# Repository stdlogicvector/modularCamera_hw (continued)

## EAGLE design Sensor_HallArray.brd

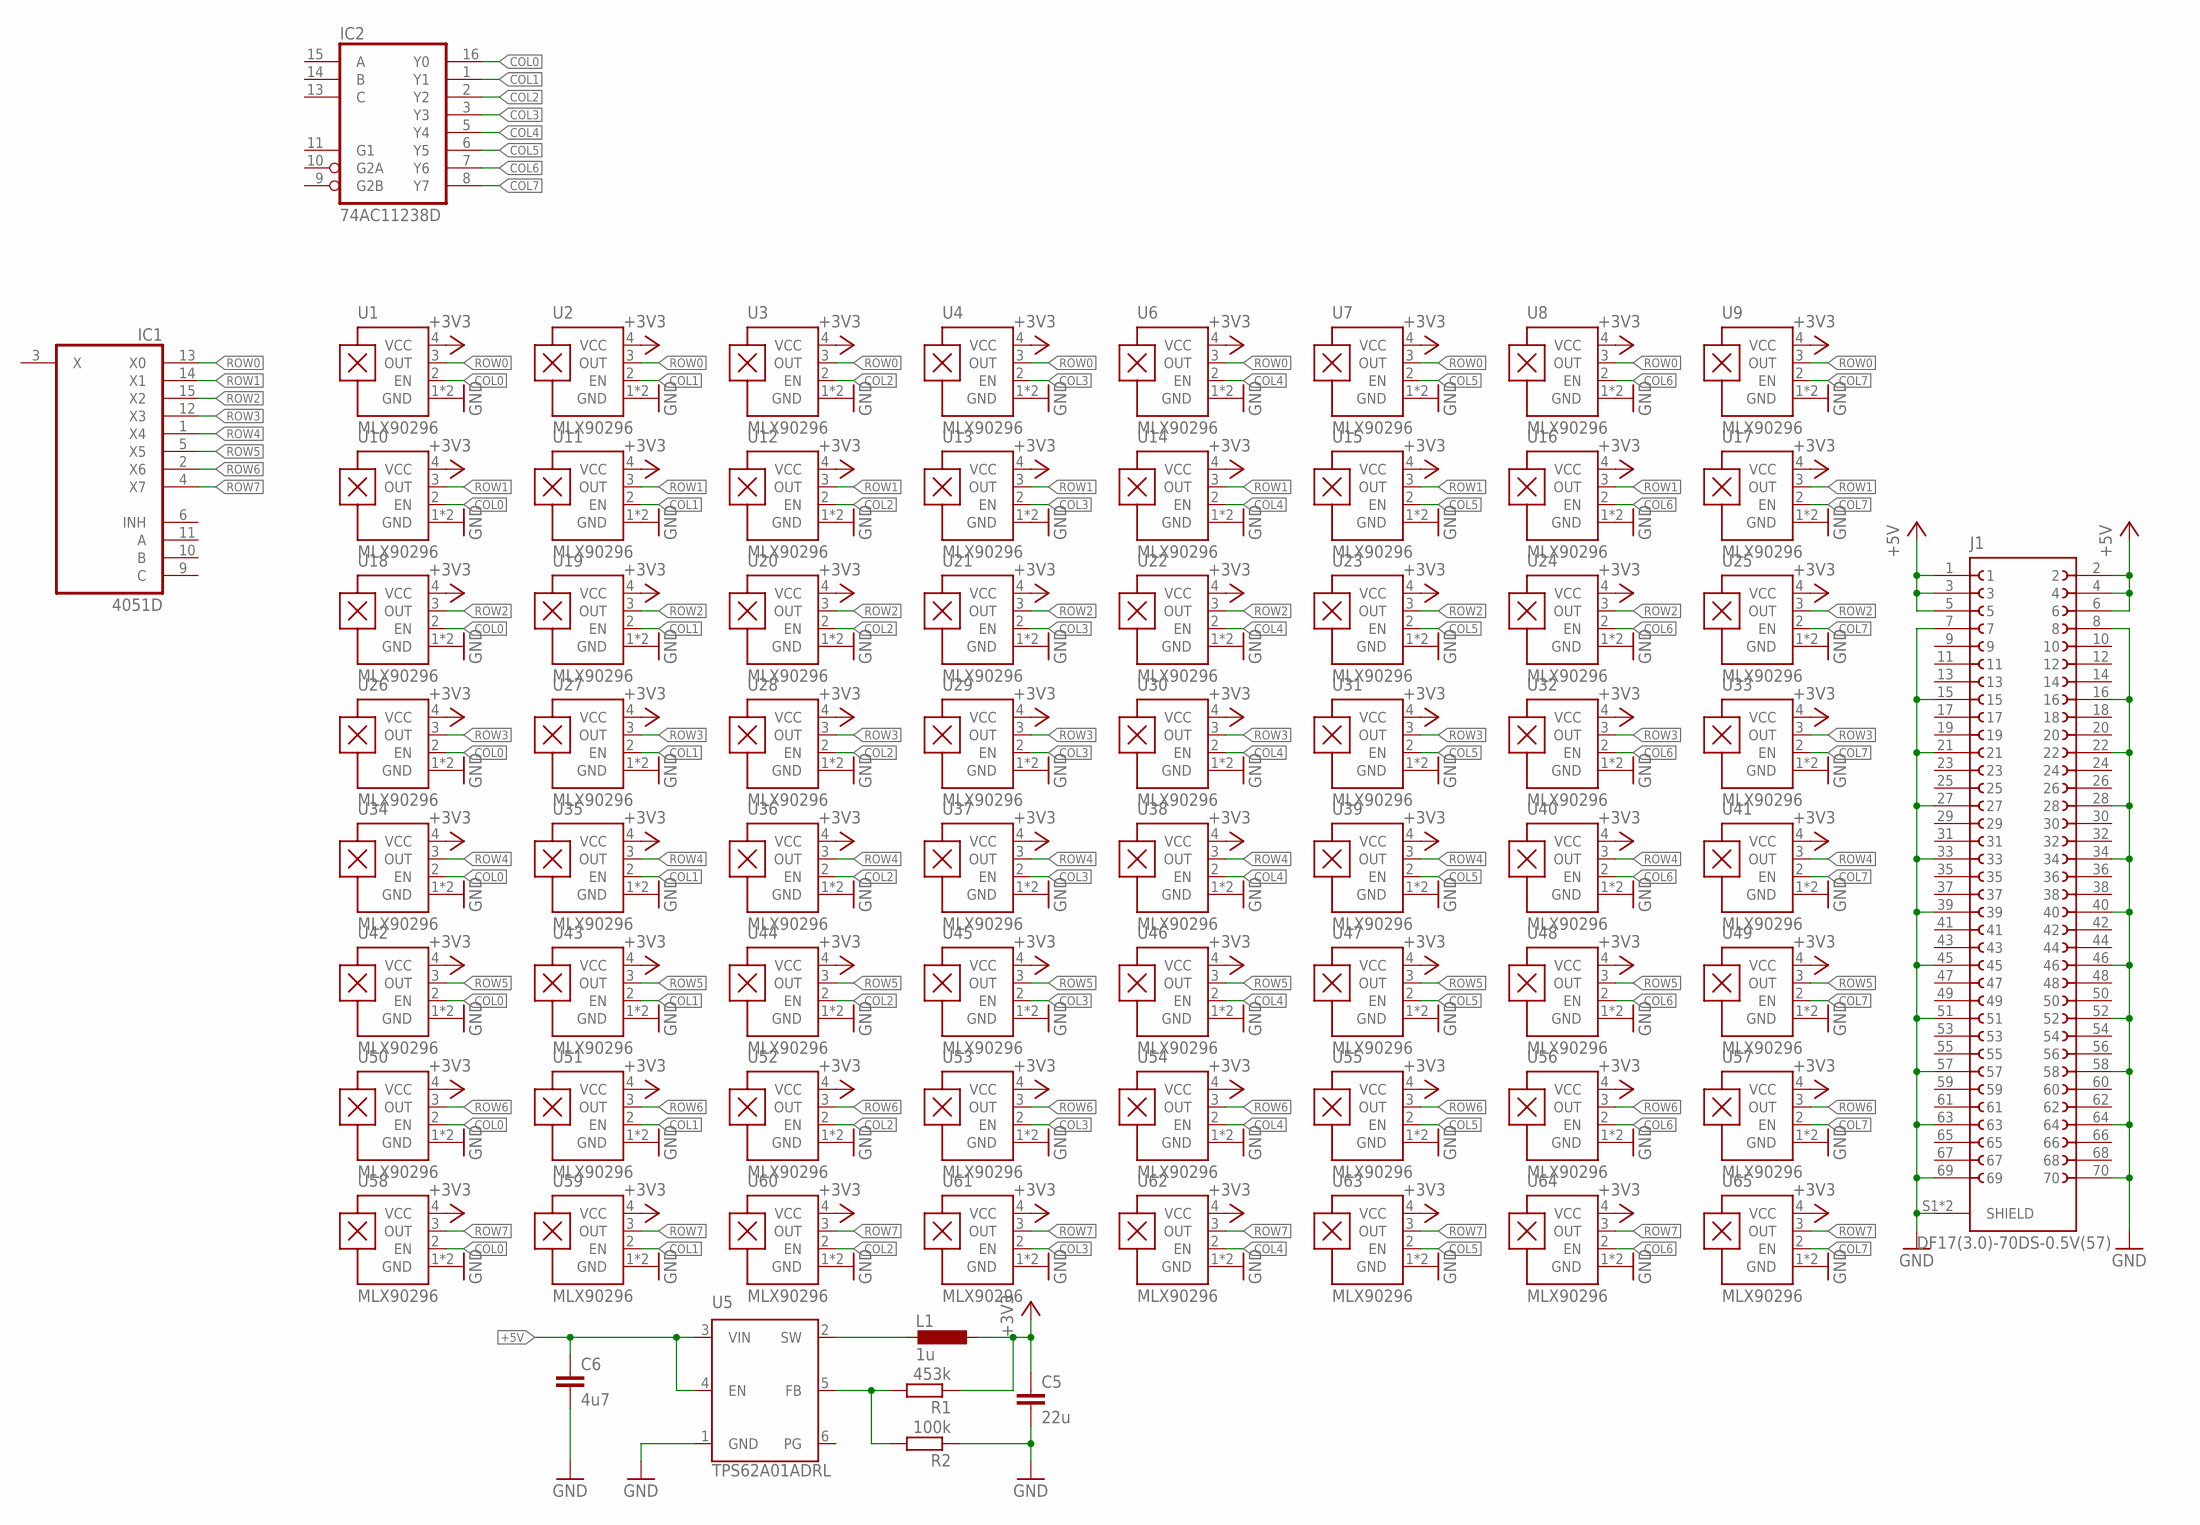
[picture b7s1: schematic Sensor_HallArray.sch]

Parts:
C5: 22u; C0603; LCSC C109448
C6: 4u7; C0603; LCSC C19666
IC1: 4051D; SO16
IC2: 74AC11238D; SO16
J1: DF17(3.0)-70DS-0.5V(57)
L1: 1u; L1008; MPN LQM2HPN1R0MG0L; DIGIKEY 490-5112-1-ND
R1: 453k; R0402; LCSC C137978
R2: 100k; R0402; DIGIKEY RMCF0402FT100KCT-ND
U1, U2, U3, U4, U6, U7, U8, U9, U10, U11, U12, U13, U14, U15, U16, U17, U18, U19, U20, U21, U22, U23, U24, U25, U26, U27, U28, U29, U30, U31, U32, U33, U34, U35, U36, U37, U38, U39, U40, U41, U42, U43, U44, U45, U46, U47, U48, U49, U50, U51, U52, U53, U54, U55, U56, U57, U58, U59, U60, U61, U62, U63, U64, U65: MLX90296; DFN120X160X40-4
U5: TPS62A01ADRL; SOTFL50P160X60-6N; DIGIKEY 296-TPS62A01ADRLRCT-ND

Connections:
+3V3: C5.1, L1.1, R1.1, U1.4 (VCC), U2.4 (VCC), U3.4 (VCC), U4.4 (VCC), U6.4 (VCC), U7.4 (VCC), U8.4 (VCC), U9.4 (VCC), U10.4 (VCC), U11.4 (VCC), U12.4 (VCC), U13.4 (VCC), U14.4 (VCC), U15.4 (VCC), U16.4 (VCC), U17.4 (VCC), U18.4 (VCC), U19.4 (VCC), U20.4 (VCC), U21.4 (VCC), U22.4 (VCC), U23.4 (VCC), U24.4 (VCC), U25.4 (VCC), U26.4 (VCC), U27.4 (VCC), U28.4 (VCC), U29.4 (VCC), U30.4 (VCC), U31.4 (VCC), U32.4 (VCC), U33.4 (VCC), U34.4 (VCC), U35.4 (VCC), U36.4 (VCC), U37.4 (VCC), U38.4 (VCC), U39.4 (VCC), U40.4 (VCC), U41.4 (VCC), U42.4 (VCC), U43.4 (VCC), U44.4 (VCC), U45.4 (VCC), U46.4 (VCC), U47.4 (VCC), U48.4 (VCC), U49.4 (VCC), U50.4 (VCC), U51.4 (VCC), U52.4 (VCC), U53.4 (VCC), U54.4 (VCC), U55.4 (VCC), U56.4 (VCC), U57.4 (VCC), U58.4 (VCC), U59.4 (VCC), U60.4 (VCC), U61.4 (VCC), U62.4 (VCC), U63.4 (VCC), U64.4 (VCC), U65.4 (VCC)
+5V: C6.1, J1.1, J1.2, J1.3, J1.4, J1.5, J1.6, U5.3 (VIN), U5.4 (EN)
COL0: IC2.16 (Y0), U1.2 (EN), U10.2 (EN), U18.2 (EN), U26.2 (EN), U34.2 (EN), U42.2 (EN), U50.2 (EN), U58.2 (EN)
COL1: IC2.1 (Y1), U2.2 (EN), U11.2 (EN), U19.2 (EN), U27.2 (EN), U35.2 (EN), U43.2 (EN), U51.2 (EN), U59.2 (EN)
COL2: IC2.2 (Y2), U3.2 (EN), U12.2 (EN), U20.2 (EN), U28.2 (EN), U36.2 (EN), U44.2 (EN), U52.2 (EN), U60.2 (EN)
COL3: IC2.3 (Y3), U4.2 (EN), U13.2 (EN), U21.2 (EN), U29.2 (EN), U37.2 (EN), U45.2 (EN), U53.2 (EN), U61.2 (EN)
COL4: IC2.5 (Y4), U6.2 (EN), U14.2 (EN), U22.2 (EN), U30.2 (EN), U38.2 (EN), U46.2 (EN), U54.2 (EN), U62.2 (EN)
COL5: IC2.6 (Y5), U7.2 (EN), U15.2 (EN), U23.2 (EN), U31.2 (EN), U39.2 (EN), U47.2 (EN), U55.2 (EN), U63.2 (EN)
COL6: IC2.7 (Y6), U8.2 (EN), U16.2 (EN), U24.2 (EN), U32.2 (EN), U40.2 (EN), U48.2 (EN), U56.2 (EN), U64.2 (EN)
COL7: IC2.8 (Y7), U9.2 (EN), U17.2 (EN), U25.2 (EN), U33.2 (EN), U41.2 (EN), U49.2 (EN), U57.2 (EN), U65.2 (EN)
GND: C5.2, C6.2, IC1.8 (GND), IC2.4 (GND), J1.7, J1.8, J1.15, J1.16, J1.21, J1.22, J1.27, J1.28, J1.33, J1.34, J1.39, J1.40, J1.45, J1.46, J1.51, J1.52, J1.57, J1.58, J1.63, J1.64, J1.69, J1.70, J1.S1 (SHIELD), J1.S2 (SHIELD), R2.1, U1.1 (GND), U1.E (GND), U2.1 (GND), U2.E (GND), U3.1 (GND), U3.E (GND), U4.1 (GND), U4.E (GND), U5.1 (GND), U6.1 (GND), U6.E (GND), U7.1 (GND), U7.E (GND), U8.1 (GND), U8.E (GND), U9.1 (GND), U9.E (GND), U10.1 (GND), U10.E (GND), U11.1 (GND), U11.E (GND), U12.1 (GND), U12.E (GND), U13.1 (GND), U13.E (GND), U14.1 (GND), U14.E (GND), U15.1 (GND), U15.E (GND), U16.1 (GND), U16.E (GND), U17.1 (GND), U17.E (GND), U18.1 (GND), U18.E (GND), U19.1 (GND), U19.E (GND), U20.1 (GND), U20.E (GND), U21.1 (GND), U21.E (GND), U22.1 (GND), U22.E (GND), U23.1 (GND), U23.E (GND), U24.1 (GND), U24.E (GND), U25.1 (GND), U25.E (GND), U26.1 (GND), U26.E (GND), U27.1 (GND), U27.E (GND), U28.1 (GND), U28.E (GND), U29.1 (GND), U29.E (GND), U30.1 (GND), U30.E (GND), U31.1 (GND), U31.E (GND), U32.1 (GND), U32.E (GND), U33.1 (GND), U33.E (GND), U34.1 (GND), U34.E (GND), U35.1 (GND), U35.E (GND), U36.1 (GND), U36.E (GND), U37.1 (GND), U37.E (GND), U38.1 (GND), U38.E (GND), U39.1 (GND), U39.E (GND), U40.1 (GND), U40.E (GND), U41.1 (GND), U41.E (GND), U42.1 (GND), U42.E (GND), U43.1 (GND), U43.E (GND), U44.1 (GND), U44.E (GND), U45.1 (GND), U45.E (GND), U46.1 (GND), U46.E (GND), U47.1 (GND), U47.E (GND), U48.1 (GND), U48.E (GND), U49.1 (GND), U49.E (GND), U50.1 (GND), U50.E (GND), U51.1 (GND), U51.E (GND), U52.1 (GND), U52.E (GND), U53.1 (GND), U53.E (GND), U54.1 (GND), U54.E (GND), U55.1 (GND), U55.E (GND), U56.1 (GND), U56.E (GND), U57.1 (GND), U57.E (GND), U58.1 (GND), U58.E (GND), U59.1 (GND), U59.E (GND), U60.1 (GND), U60.E (GND), U61.1 (GND), U61.E (GND), U62.1 (GND), U62.E (GND), U63.1 (GND), U63.E (GND), U64.1 (GND), U64.E (GND), U65.1 (GND), U65.E (GND)
unnamed: R1.2, R2.2, U5.5 (FB)
unnamed: L1.2, U5.2 (SW)
ROW0: IC1.13 (X0), U1.3 (OUT), U2.3 (OUT), U3.3 (OUT), U4.3 (OUT), U6.3 (OUT), U7.3 (OUT), U8.3 (OUT), U9.3 (OUT)
ROW1: IC1.14 (X1), U10.3 (OUT), U11.3 (OUT), U12.3 (OUT), U13.3 (OUT), U14.3 (OUT), U15.3 (OUT), U16.3 (OUT), U17.3 (OUT)
ROW2: IC1.15 (X2), U18.3 (OUT), U19.3 (OUT), U20.3 (OUT), U21.3 (OUT), U22.3 (OUT), U23.3 (OUT), U24.3 (OUT), U25.3 (OUT)
ROW3: IC1.12 (X3), U26.3 (OUT), U27.3 (OUT), U28.3 (OUT), U29.3 (OUT), U30.3 (OUT), U31.3 (OUT), U32.3 (OUT), U33.3 (OUT)
ROW4: IC1.1 (X4), U34.3 (OUT), U35.3 (OUT), U36.3 (OUT), U37.3 (OUT), U38.3 (OUT), U39.3 (OUT), U40.3 (OUT), U41.3 (OUT)
ROW5: IC1.5 (X5), U42.3 (OUT), U43.3 (OUT), U44.3 (OUT), U45.3 (OUT), U46.3 (OUT), U47.3 (OUT), U48.3 (OUT), U49.3 (OUT)
ROW6: IC1.2 (X6), U50.3 (OUT), U51.3 (OUT), U52.3 (OUT), U53.3 (OUT), U54.3 (OUT), U55.3 (OUT), U56.3 (OUT), U57.3 (OUT)
ROW7: IC1.4 (X7), U58.3 (OUT), U59.3 (OUT), U60.3 (OUT), U61.3 (OUT), U62.3 (OUT), U63.3 (OUT), U64.3 (OUT), U65.3 (OUT)
VCC: IC1.16 (VCC), IC2.12 (VCC)
VEE: IC1.7 (VEE)

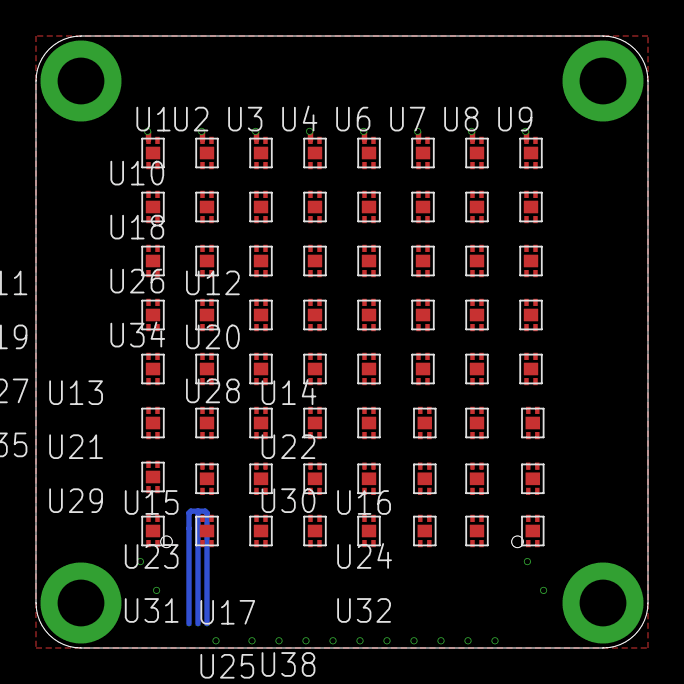
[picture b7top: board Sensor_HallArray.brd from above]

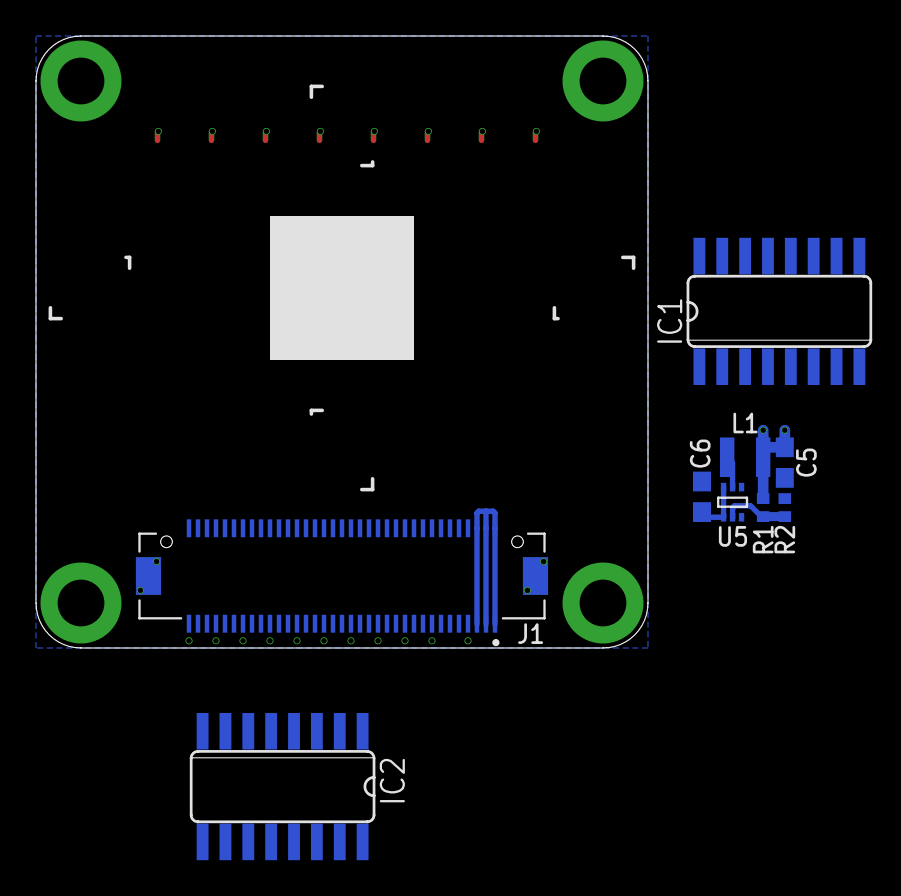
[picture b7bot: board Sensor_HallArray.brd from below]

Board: 4 copper layers, 34.0 x 34.0 mm, 73 parts (9 on the bottom side), 22 nets.

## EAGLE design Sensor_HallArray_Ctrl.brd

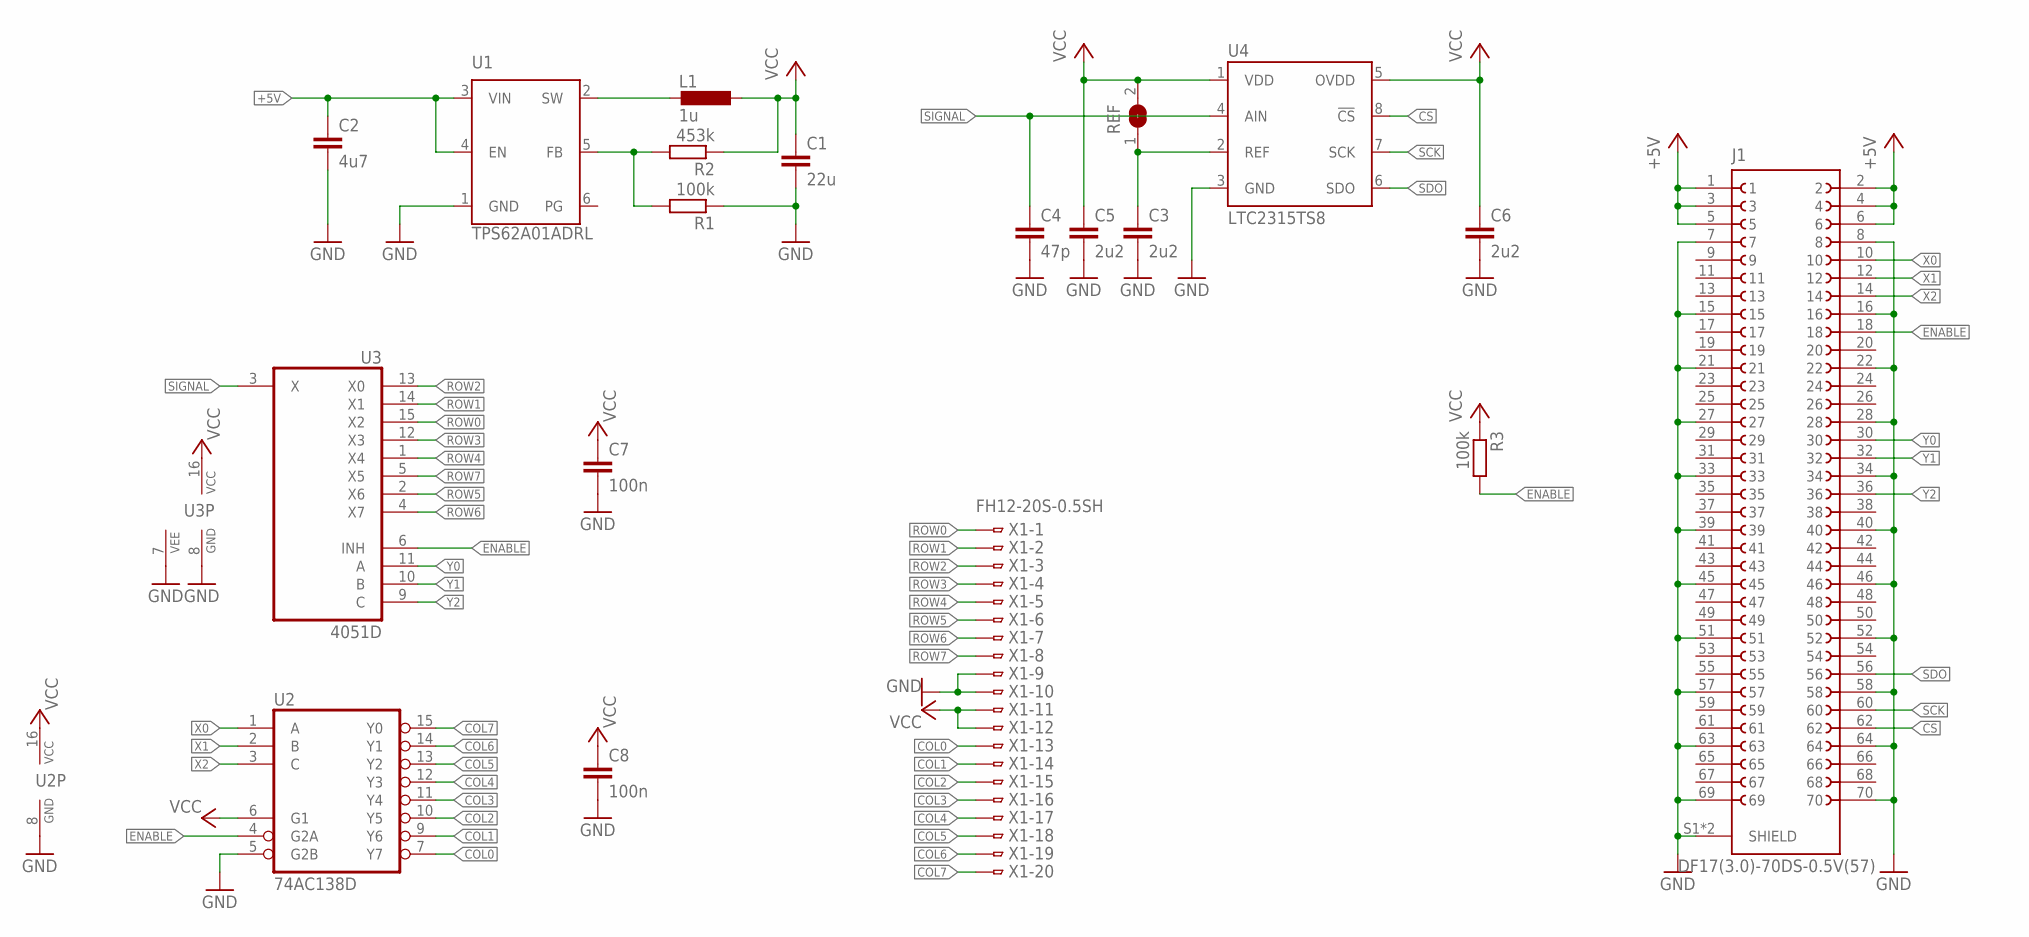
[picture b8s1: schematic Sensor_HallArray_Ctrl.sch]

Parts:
C1: 22u; C0603; LCSC C109448
C2: 4u7; C0603; LCSC C19666
C3, C5, C6: 2u2; C0603; LCSC C19666
C4: 47p; C0402
C7, C8: 100n; C0402
J1: DF17(3.0)-70DS-0.5V(57)
L1: 1u; L1008; MPN LQM2HPN1R0MG0L; DIGIKEY 490-5112-1-ND
R1, R3: 100k; R0402; DIGIKEY RMCF0402FT100KCT-ND
R2: 453k; R0402; LCSC C137978
REF: SJ
U1: TPS62A01ADRL; SOTFL50P160X60-6N; DIGIKEY 296-TPS62A01ADRLRCT-ND
U2: 74AC138D; SO16
U3: 4051D; SO16
U4: LTC2315TS8; SOT23-8L
X1: FH12-20S-0.5SH

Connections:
!CS: J1.62, U4.8 (!CS)
!ENABLE: J1.18, R3.2, U2.4 (G2A), U3.6 (INH)
+5V: C2.1, J1.1, J1.2, J1.3, J1.4, J1.5, J1.6, U1.3 (VIN), U1.4 (EN)
COL0: U2.7 (Y7), X1.13
COL1: U2.9 (Y6), X1.14
COL2: U2.10 (Y5), X1.15
COL3: U2.11 (Y4), X1.16
COL4: U2.12 (Y3), X1.17
COL5: U2.13 (Y2), X1.18
COL6: U2.14 (Y1), X1.19
COL7: U2.15 (Y0), X1.20
GND: C1.2, C2.2, C3.2, C4.2, C5.2, C6.2, C7.2, C8.2, J1.7, J1.8, J1.15, J1.16, J1.21, J1.22, J1.27, J1.28, J1.33, J1.34, J1.39, J1.40, J1.45, J1.46, J1.51, J1.52, J1.57, J1.58, J1.63, J1.64, J1.69, J1.70, J1.S1 (SHIELD), J1.S2 (SHIELD), R1.1, U1.1 (GND), U2.5 (G2B), U2.8 (GND), U3.7 (VEE), U3.8 (GND), U4.3 (GND), X1.9, X1.10
unnamed: R1.2, R2.2, U1.5 (FB)
unnamed: L1.2, U1.2 (SW)
unnamed: C3.1, REF.1, U4.2 (REF)
ROW0: U3.15 (X2), X1.1
ROW1: U3.14 (X1), X1.2
ROW2: U3.13 (X0), X1.3
ROW3: U3.12 (X3), X1.4
ROW4: U3.1 (X4), X1.5
ROW5: U3.2 (X6), X1.6
ROW6: U3.4 (X7), X1.7
ROW7: U3.5 (X5), X1.8
SCK: J1.60, U4.7 (SCK)
SDO: J1.56, U4.6 (SDO)
SIGNAL: C4.1, U3.3 (X), U4.4 (AIN)
VCC: C1.1, C5.1, C6.1, C7.1, C8.1, L1.1, R2.1, R3.1, REF.2, U2.6 (G1), U2.16 (VCC), U3.16 (VCC), U4.1 (VDD), U4.5 (OVDD), X1.11, X1.12
X0: J1.10, U2.1 (A)
X1: J1.12, U2.2 (B)
X2: J1.14, U2.3 (C)
Y0: J1.30, U3.11 (A)
Y1: J1.32, U3.10 (B)
Y2: J1.36, U3.9 (C)

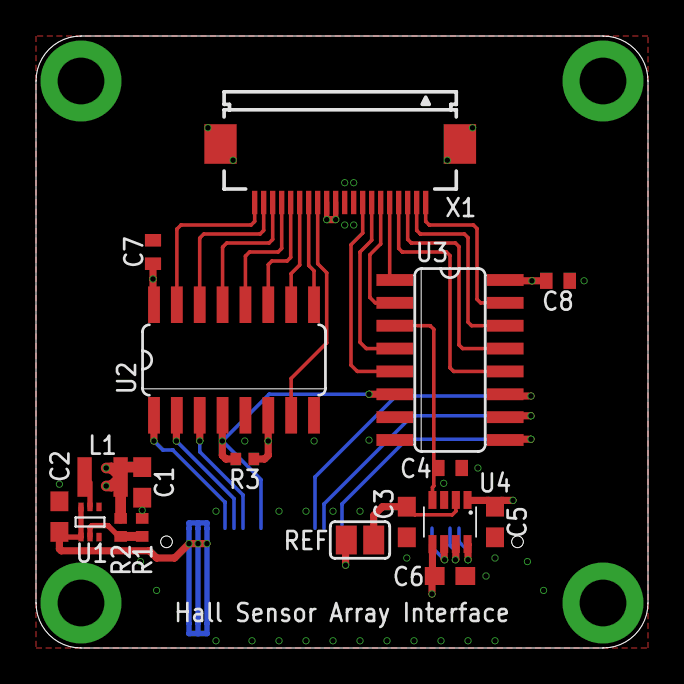
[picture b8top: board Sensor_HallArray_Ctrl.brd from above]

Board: 4 copper layers, 34.0 x 34.0 mm, 19 parts (1 on the bottom side), 33 nets.
